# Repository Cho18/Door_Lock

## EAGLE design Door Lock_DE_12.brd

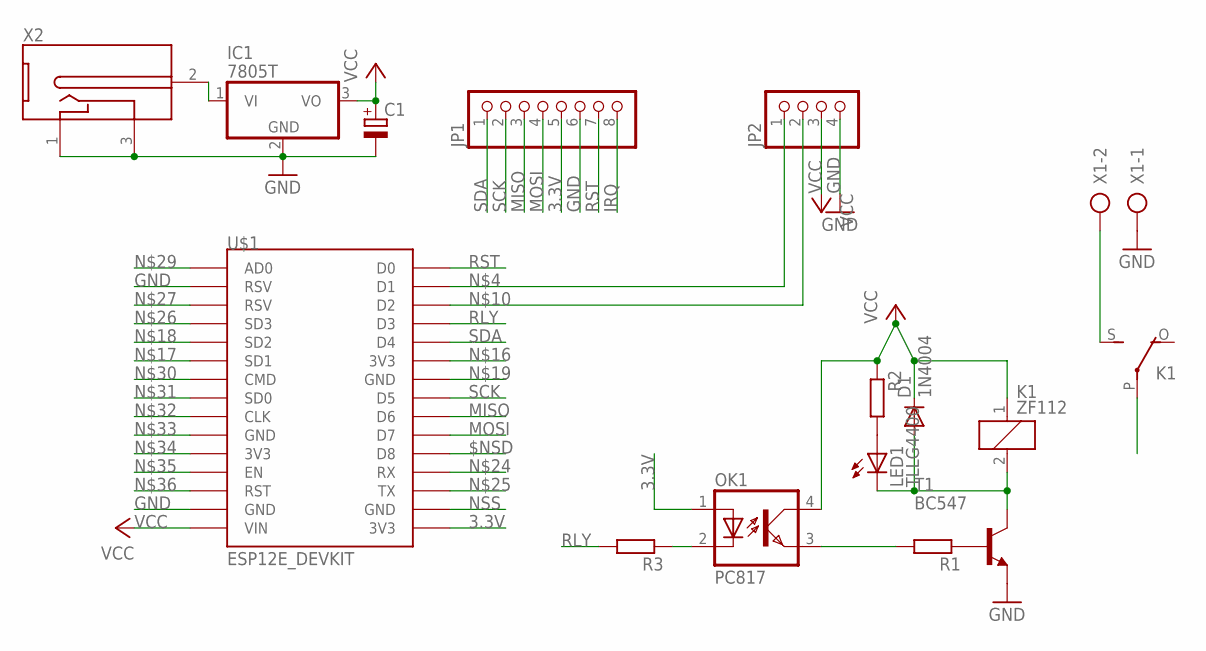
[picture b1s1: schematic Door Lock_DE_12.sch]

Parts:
C1: CPOL-EUE3.5-8; E3,5-8
D1: 1N4004; DO41-10
IC1: 7805T; TO220H
JP1: PINHD-1X8; 1X08
JP2: PINHD-1X4; 1X04
K1: ZF112
LED1: TLLG4400; LED3MM
OK1: PC817; DIL04
R1, R2, R3: R-EU_0204/7; 0204/7
T1: BC547; TO92
U$1: ESP12E_DEVKIT
X1: AK300/2
X2: DC-2.1MM-5MM; DC-21MM

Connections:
3.3V: JP1.5, OK1.1 (A), U$1.3V3@2 (3V3)
$NSD: U$1.D8
GND: C1.-, IC1.2 (GND), JP1.6, JP2.4, T1.1 (E), U$1.GND@1 (GND), U$1.RSV@0 (RSV), X1.1, X2.1, X2.3 (2)
IRQ: JP1.8
MISO: JP1.3, U$1.D6
MOSI: JP1.4, U$1.D7
unnamed: LED1.A, R2.2
unnamed: R1.1, T1.2 (B)
unnamed: JP2.1, U$1.D1
unnamed: IC1.1 (VI), X2.2 (3)
unnamed: K1.S, X1.2
unnamed: D1.A, K1.2, LED1.K (C), T1.3 (C)
unnamed: OK1.3 (EMIT), R1.2
unnamed: OK1.2 (C), R3.1
unnamed: JP2.2, U$1.D2
NSS: U$1.GND@3 (GND)
RLY: R3.2, U$1.D3
RST: JP1.7, U$1.D0
SCK: JP1.2, U$1.D5
SDA: JP1.1, U$1.D4
VCC: C1.+, D1.C, IC1.3 (VO), JP2.3, K1.1, K1.P, OK1.4 (COL), R2.1, U$1.VIN

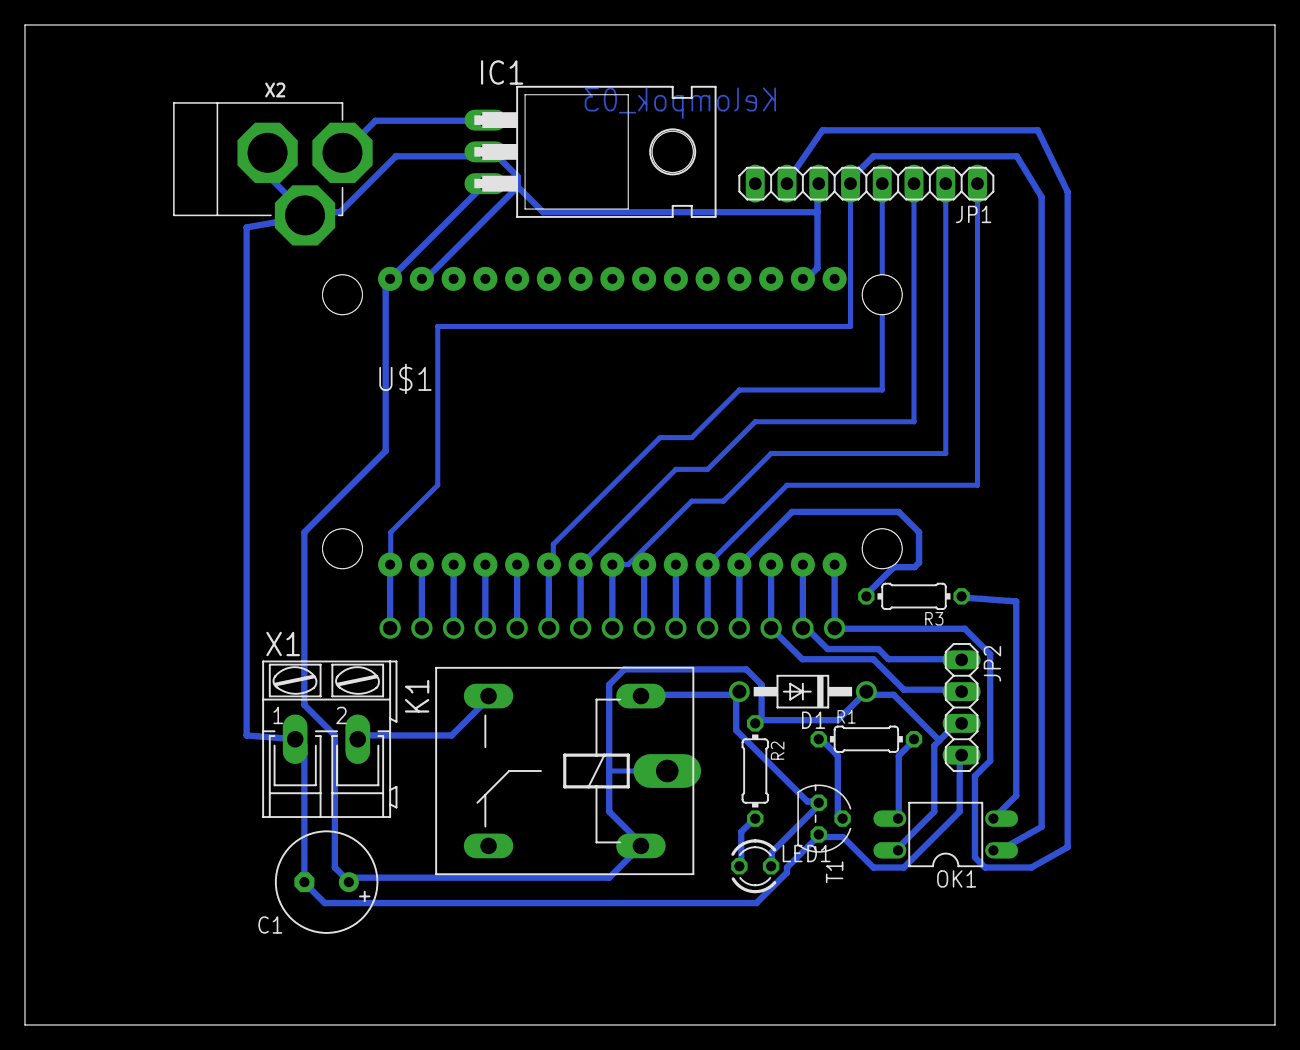
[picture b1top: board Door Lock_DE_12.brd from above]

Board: 2 copper layers, 100.0 x 80.0 mm, 15 parts (0 on the bottom side), 18 nets.

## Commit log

2023-09-08 Door Lock
